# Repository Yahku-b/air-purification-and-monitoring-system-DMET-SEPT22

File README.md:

# air-purification-and-monitoring-system-DMET-SEPT22
MANAGE PROJECTS EXERCISE

Team

Name of Team Member	Roles

Jacob mutiso	mechanical and project management

Patrick gichuke	 electrical and simulation

Technologies
1.	Mechanical/hardware design- AUTO DESK, PROTEUS
2.	Electrical and PCB electronic components- KI CAD, PROTEUS
3.	Programming and control- ARDUINO software
4.	Project management tool- Github and Trello apps

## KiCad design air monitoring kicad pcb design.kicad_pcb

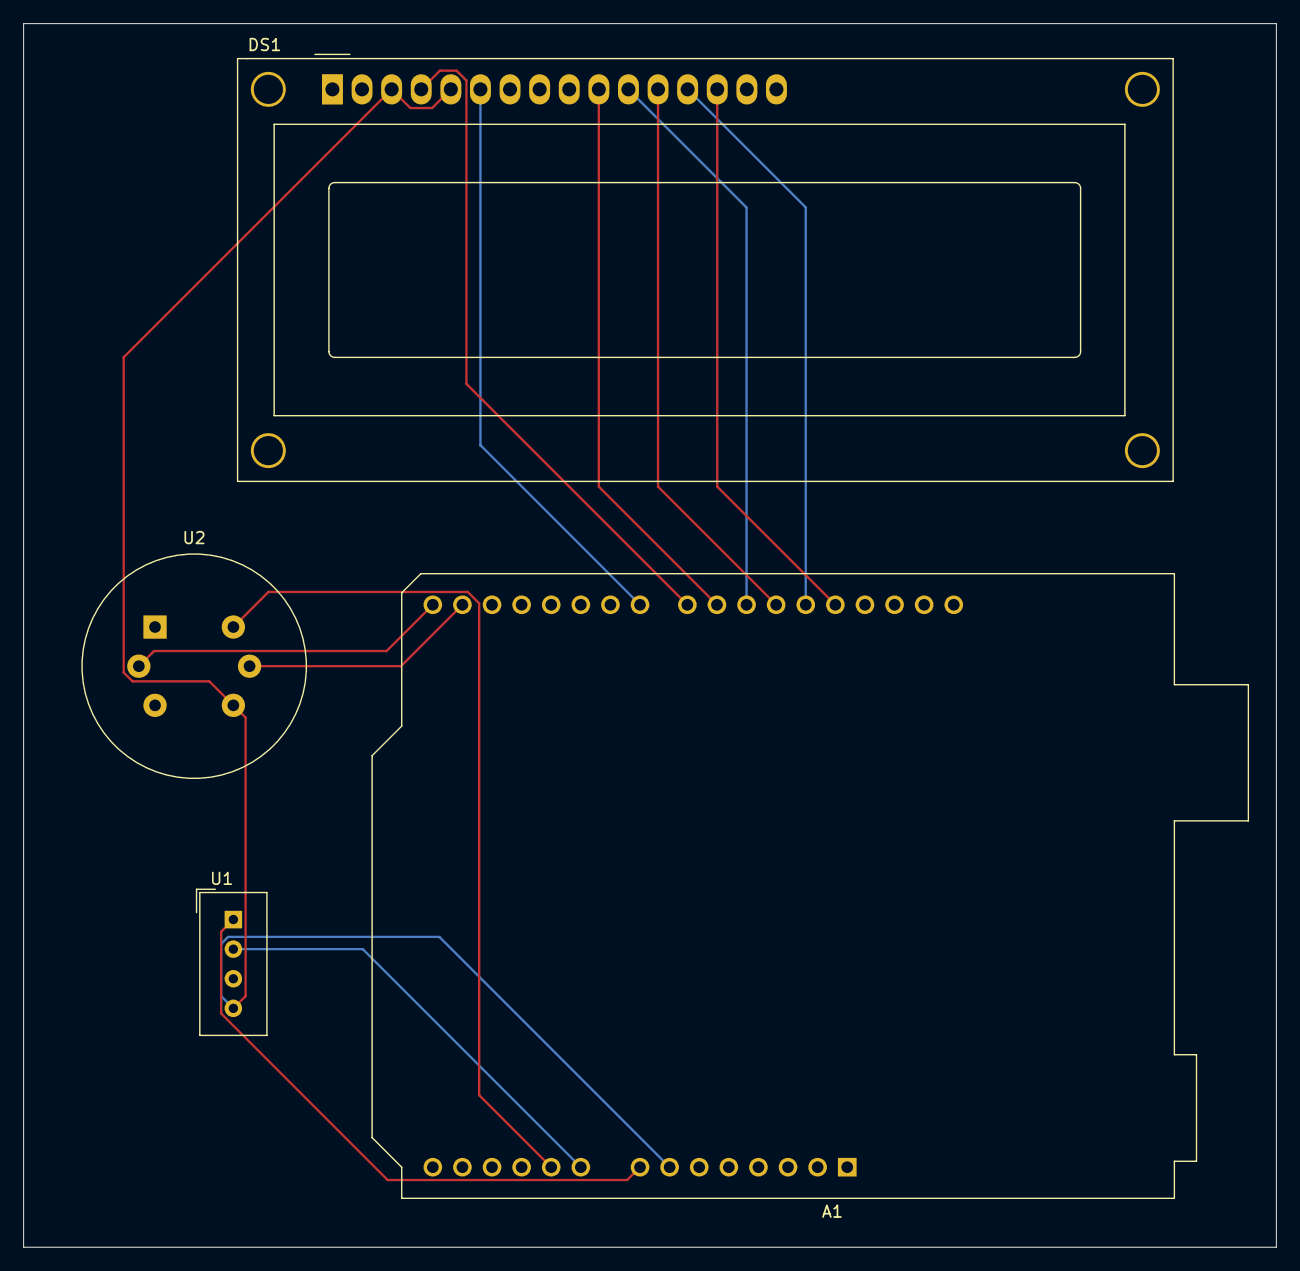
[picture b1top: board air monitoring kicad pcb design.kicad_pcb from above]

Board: 2 copper layers, 107.5 x 105.0 mm, 4 parts (0 on the bottom side), 13 nets.

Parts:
A1: Arduino_UNO_R3
DS1: WC1602A
U1: DHT11; Aosong_DHT11_5.5x12.0_P2.54mm
U2: MQ-6

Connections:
GNDREF: A1.7 (GND), DS1.3 (VO), DS1.5 (R/W), U1.4 (GND), U2.4 (A2)
unnamed: A1.9 (A0), U1.2 (DATA)
unnamed: A1.10 (A1), U2.6 (A1)
unnamed: A1.15 (D0/RX), U2.2 (VH+)
unnamed: A1.16 (D1/TX), U2.5 (VH-)
unnamed: A1.22 (D7), DS1.6 (E)
unnamed: A1.23 (D8), DS1.4 (RS)
unnamed: A1.24 (D9), DS1.10 (D3)
unnamed: A1.25 (D10), DS1.11 (D4)
unnamed: A1.26 (D11), DS1.12 (D5)
unnamed: A1.27 (D12), DS1.13 (D6)
unnamed: A1.28 (D13), DS1.14 (D7)
unnamed: A1.8 (VIN), U1.1 (VDD)
